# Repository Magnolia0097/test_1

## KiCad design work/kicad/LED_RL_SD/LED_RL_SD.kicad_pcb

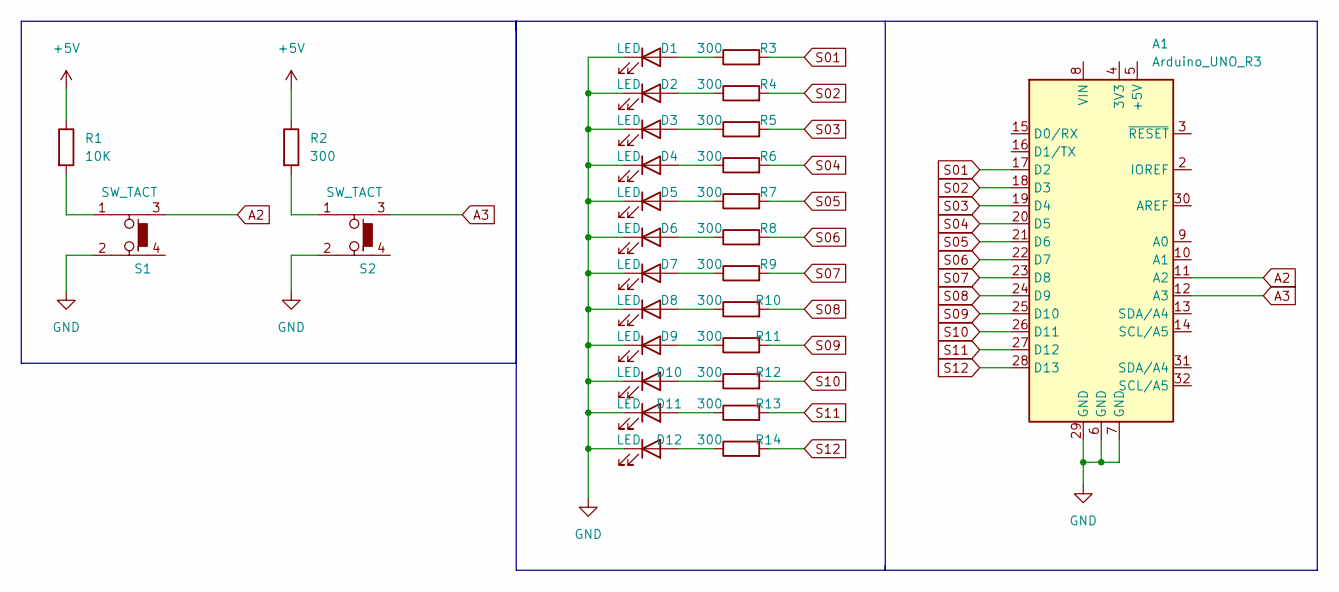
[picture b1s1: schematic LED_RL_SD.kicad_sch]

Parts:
A1: Arduino_UNO_R3
D1, D2, D3, D4, D5, D6, D7, D8, D9, D10, D11, D12: LED; LED_D5.0mm
R1: 10K; R_Axial_DIN0207_L6.3mm_D2.5mm_P7.62mm_Horizontal
R2, R3, R4, R5, R6, R7, R8, R9, R10, R11, R12, R13, R14: 300; R_Axial_DIN0207_L6.3mm_D2.5mm_P7.62mm_Horizontal
S1, S2: SW_TACT; TACT_SW

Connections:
+5V: R1.1, R2.1
A2: A1.11 (A2), S1.3
A3: A1.12 (A3), S2.3
GND: A1.6 (GND), A1.7 (GND), A1.29 (GND), D1.1 (K), D2.1 (K), D3.1 (K), D4.1 (K), D5.1 (K), D6.1 (K), D7.1 (K), D8.1 (K), D9.1 (K), D10.1 (K), D11.1 (K), D12.1 (K), S1.2, S2.2
unnamed: D1.2 (A), R3.1
unnamed: D2.2 (A), R4.1
unnamed: D3.2 (A), R5.1
unnamed: D4.2 (A), R6.1
unnamed: D5.2 (A), R7.1
unnamed: D6.2 (A), R8.1
unnamed: D7.2 (A), R9.1
unnamed: D8.2 (A), R10.1
unnamed: D9.2 (A), R11.1
unnamed: D10.2 (A), R12.1
unnamed: D11.2 (A), R13.1
unnamed: D12.2 (A), R14.1
unnamed: R1.2, S1.1
unnamed: R2.2, S2.1
S01: A1.17 (D2), R3.2
S02: A1.18 (D3), R4.2
S03: A1.19 (D4), R5.2
S04: A1.20 (D5), R6.2
S05: A1.21 (D6), R7.2
S06: A1.22 (D7), R8.2
S07: A1.23 (D8), R9.2
S08: A1.24 (D9), R10.2
S09: A1.25 (D10), R11.2
S10: A1.26 (D11), R12.2
S11: A1.27 (D12), R13.2
S12: A1.28 (D13), R14.2

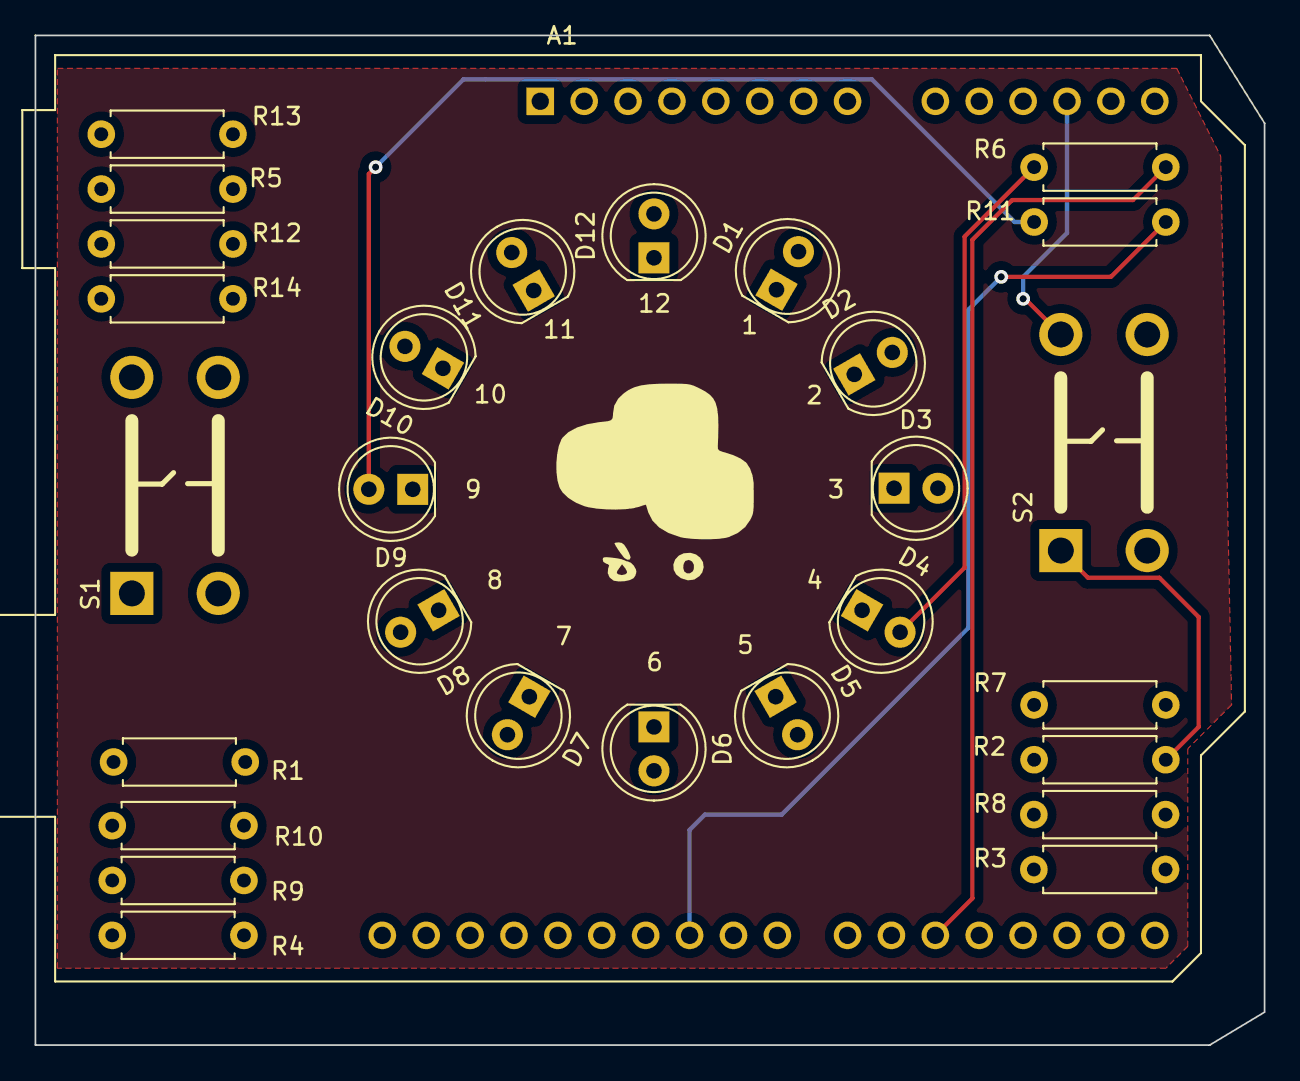
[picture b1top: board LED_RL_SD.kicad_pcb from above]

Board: 2 copper layers, 71.1 x 58.4 mm, 29 parts (0 on the bottom side), 30 nets.

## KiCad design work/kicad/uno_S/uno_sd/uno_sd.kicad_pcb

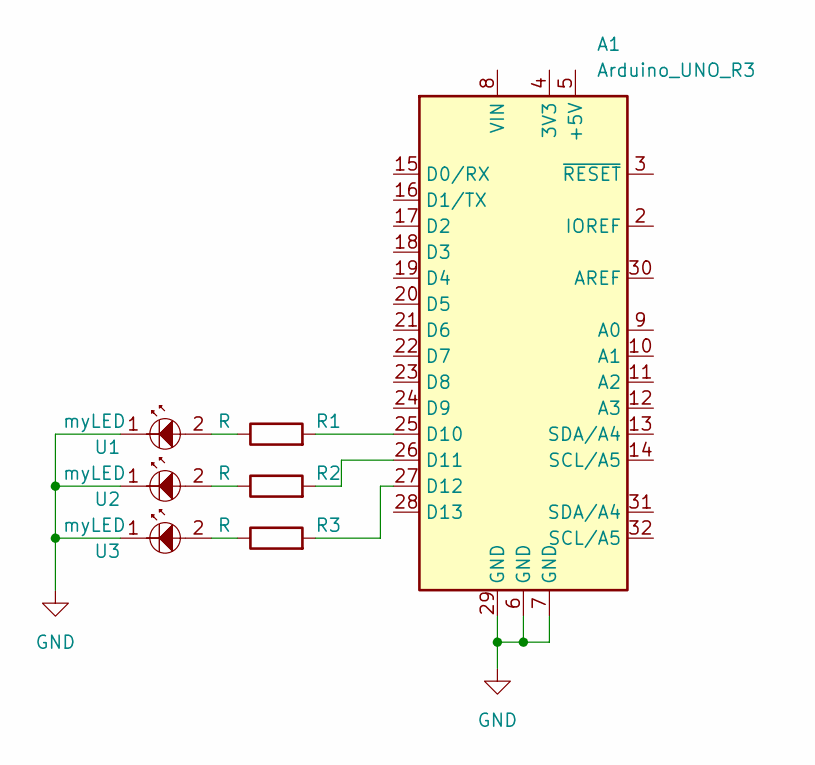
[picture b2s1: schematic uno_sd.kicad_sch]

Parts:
A1: Arduino_UNO_R3
R1, R2, R3: R; MyR
U1, U2, U3: myLED

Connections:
GND: A1.6 (GND), A1.7 (GND), A1.29 (GND), U1.1, U2.1, U3.1
unnamed: A1.25 (D10), R1.2
unnamed: A1.26 (D11), R2.2
unnamed: A1.27 (D12), R3.2
unnamed: R1.1, U1.2
unnamed: R2.1, U2.2
unnamed: R3.1, U3.2

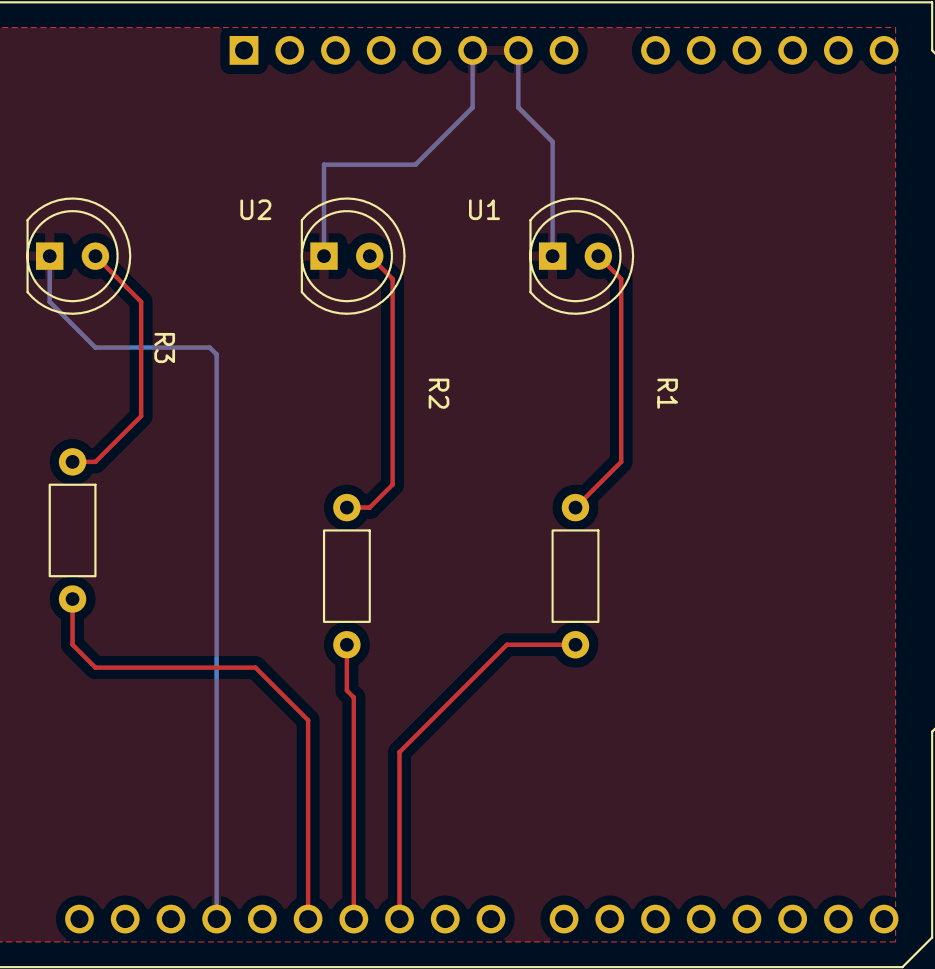
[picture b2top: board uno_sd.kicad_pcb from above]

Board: 2 copper layers, 7 parts (0 on the bottom side), 7 nets.

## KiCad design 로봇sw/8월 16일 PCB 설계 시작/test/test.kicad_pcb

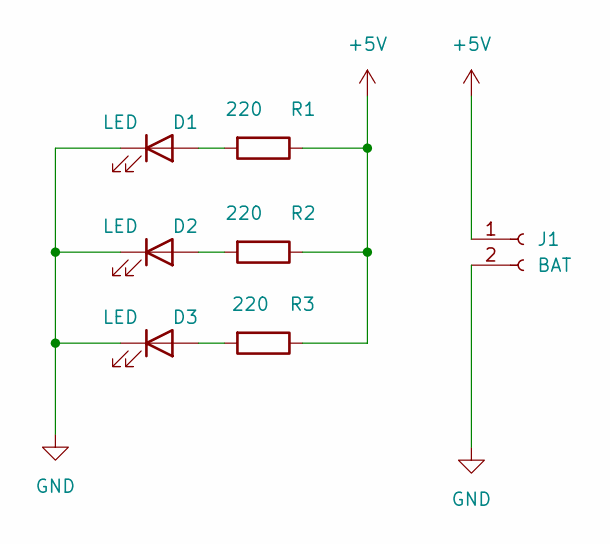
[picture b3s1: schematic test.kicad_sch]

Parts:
D1, D2, D3: LED; LED_D5.0mm
J1: BAT; Molex_SPOX_5267-02A_1x02_P2.50mm_Vertical
R1, R2, R3: 220; R_Axial_DIN0207_L6.3mm_D2.5mm_P7.62mm_Horizontal

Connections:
+5V: J1.1, R1.1, R2.1, R3.1
GND: D1.1 (K), D2.1 (K), D3.1 (K), J1.2
unnamed: D1.2 (A), R1.2
unnamed: D2.2 (A), R2.2
unnamed: D3.2 (A), R3.2

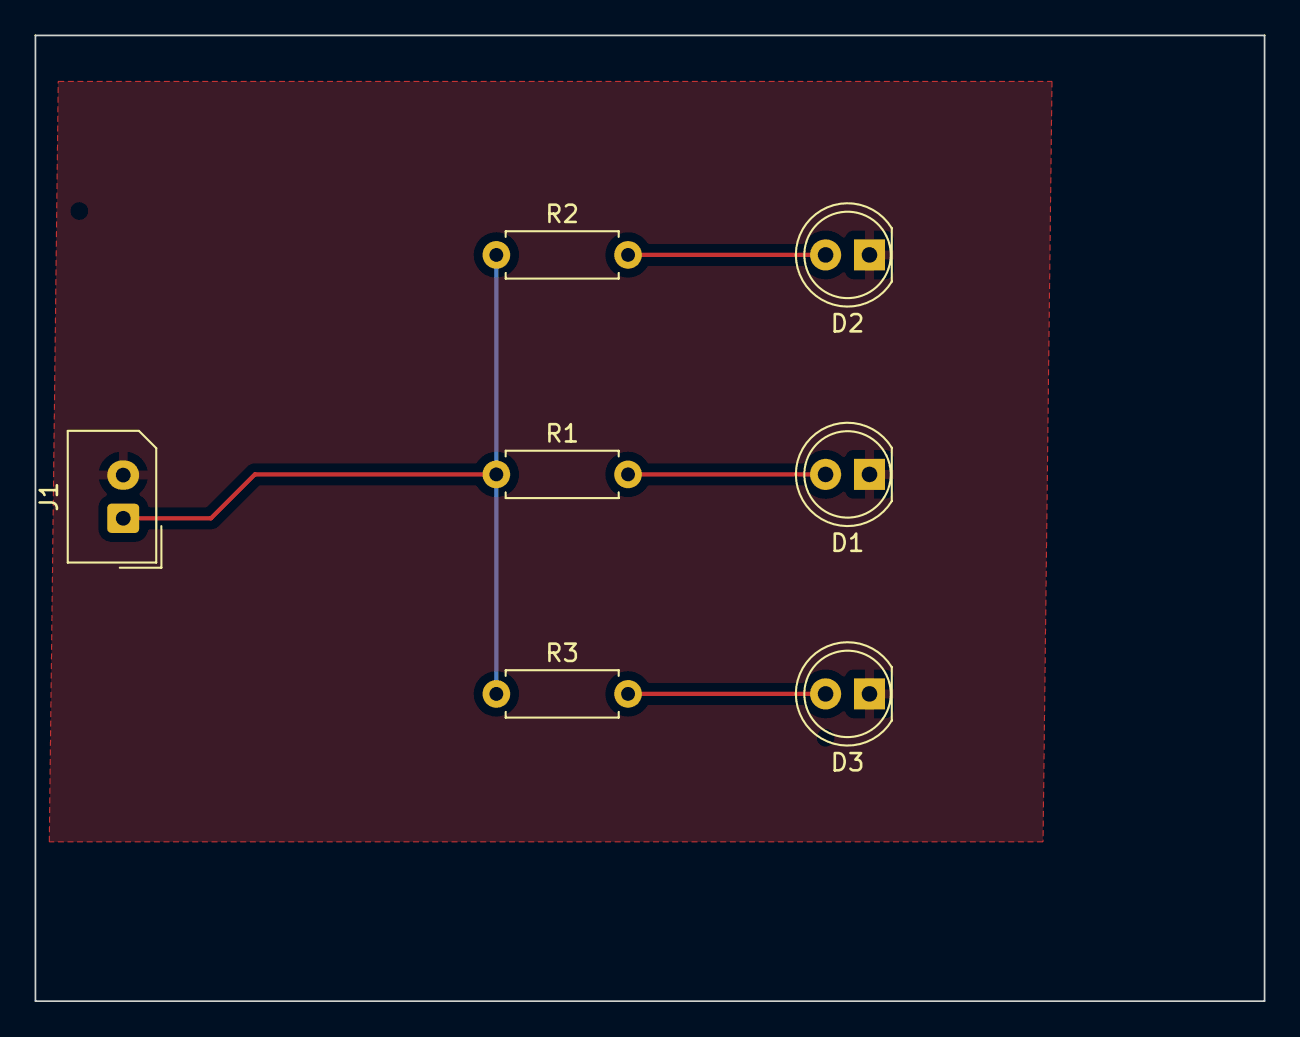
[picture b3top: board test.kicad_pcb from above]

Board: 2 copper layers, 71.1 x 55.9 mm, 7 parts (0 on the bottom side), 5 nets.

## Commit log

2022-07-26 test_220726
2022-07-26 Arduino Study at 2022-07-26-[12:02]
2022-07-26 Arduino Study at 2022-07-26-[17:41]
2022-07-26 Arduino Study at 2022-07-26-[19:30]
2022-07-27 Arduino Study at 2022-07-28-[ 8:53]
2022-07-28 Arduino Study at 2022-07-29-[ 8:54]
2022-07-29 Arduino Study at 2022-07-29-[17:32]
2022-08-02 Arduino Study at 2022-08-02-[ 9:05]
2022-08-02 Arduino Study at 2022-08-02-[17:15]
2022-08-02 Arduino Study at 2022-08-02-[17:31]
2022-08-02 Arduino Study at 2022-08-02-[17:35]
2022-08-02 Arduino Study at 2022-08-02-[17:58]
2022-08-04 Arduino Study at 2022-08-04-[17:31]
2022-08-05 Arduino Study at 2022-08-05-[12:06]
2022-08-05 Arduino Study at 2022-08-05-[12:07]
2022-08-08 Arduino Study at 2022-08-08-[20:42]
2022-08-08 Arduino Study at 2022-08-08-[21:37]
2022-08-10 Arduino Study at 2022-08-10-[17:43]
2022-08-12 Arduino Study at 2022-08-12-[18:37]
2022-08-17 Arduino Study at 2022-08-17-[14:51]
2022-08-17 Arduino Study at 2022-08-17-[21:16]
2022-08-18 Arduino Study at 2022-08-18-[20:50]
2022-08-26 Arduino Study at 2022-08-26-[17:28]
2022-08-29 Arduino Study at 2022-08-29-[11:44]
2022-08-29 Arduino Study at 2022-08-29-[16:19]
2022-09-01 Arduino Study at 2022-09-01-[17:40]
2022-09-02 Arduino Study at 2022-09-02-[17:39]
